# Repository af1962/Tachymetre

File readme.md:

Simple tachymètre, basé sur un Arduino mini, que j'utilise pour mesurer la vitesse de rotation de la broche de ma CNC.
L'affichage de la vitesse se fait sur un écran Oled i2c 128x32.

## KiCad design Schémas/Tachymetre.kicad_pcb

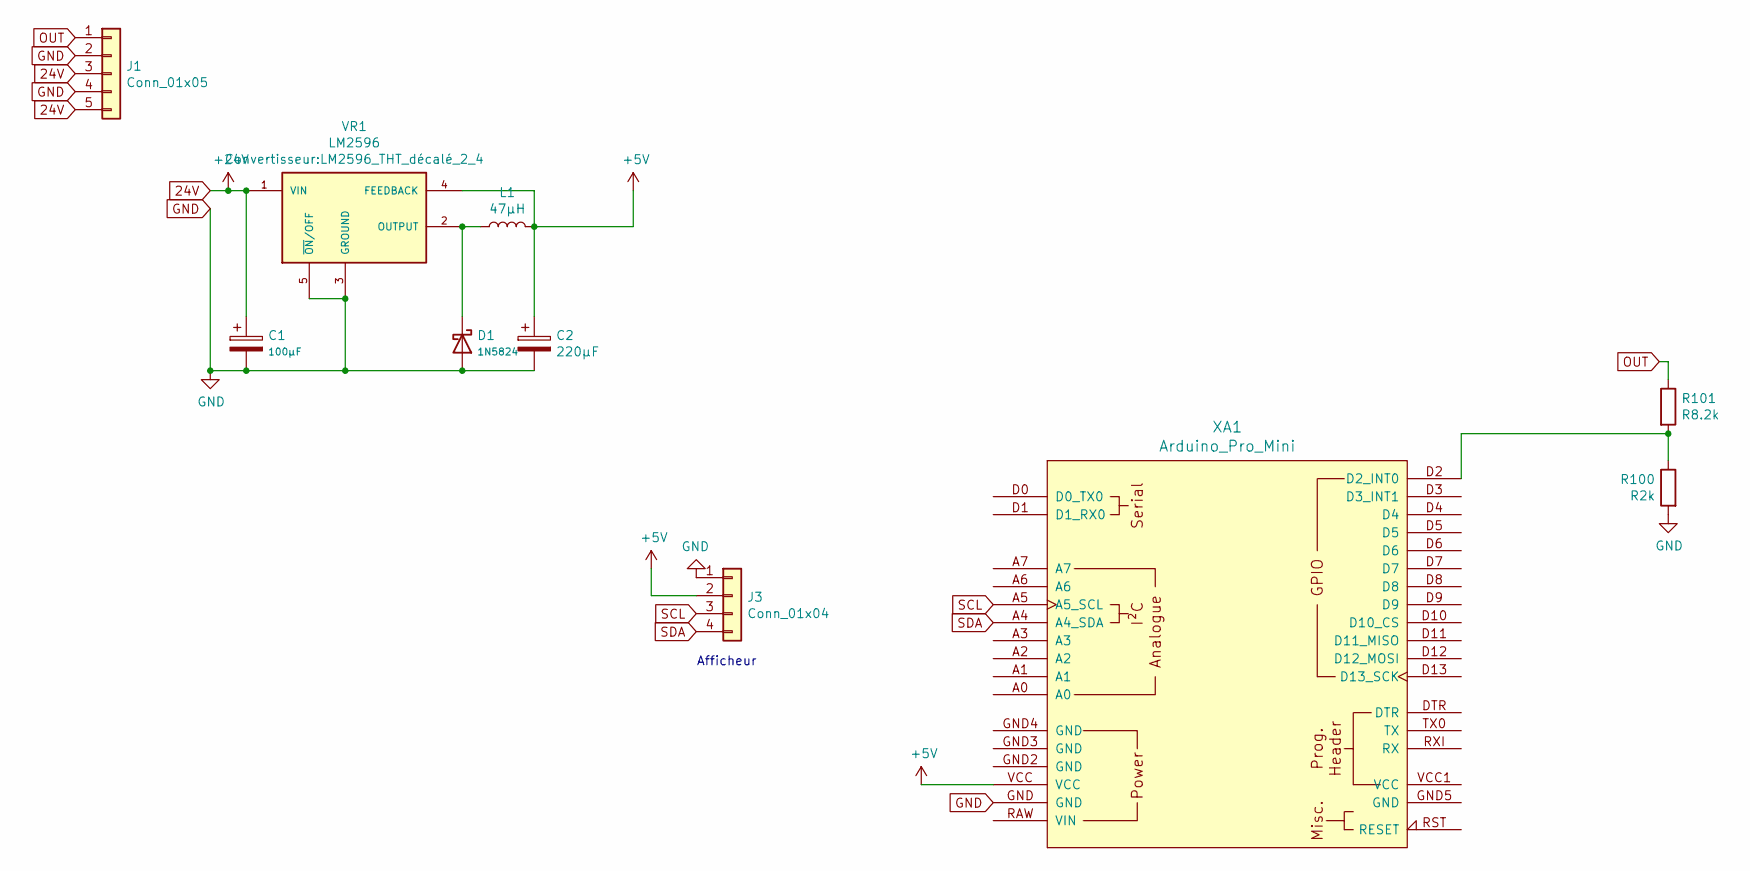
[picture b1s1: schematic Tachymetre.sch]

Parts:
C1: 100µF; CP_5x11mm
C2: 220µF; CP_10x12.5mm
D1: 1N5824; diode_do201
J1: Conn_01x05; TerminalBlock_Phoenix_MKDS-1,5-5-5.08_1x05_P5.08mm_Horizont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
J3: Conn_01x04; JST_XH_B04B-XH-A_04x2.50mm_Straight
L1: 47µH; Bobine_Toroïde
R100: R2k; R_025W
R101: R8.2k; R_025W
VR1: LM2596; LM2596_THT_décalé_2_4
XA1: Arduino_Pro_Mini

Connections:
24V: C1.1, J1.3, J1.5, VR1.1 (VIN)
+5V: C2.1, J3.2, L1.2, VR1.4 (FEEDBACK), XA1.VCC
GND: C1.2, C2.2, D1.2 (A), J1.2, J1.4, J3.1, R100.2, VR1.3 (GROUND), VR1.5 (~ON~/OFF), XA1.GND
unnamed: D1.1 (K), L1.1, VR1.2 (OUTPUT)
unnamed: R100.1, R101.2, XA1.D2 (D2_INT0)
OUT: J1.1, R101.1
SCL: J3.3, XA1.A5 (A5_SCL)
SDA: J3.4, XA1.A4 (A4_SDA)

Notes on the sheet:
Afficheur

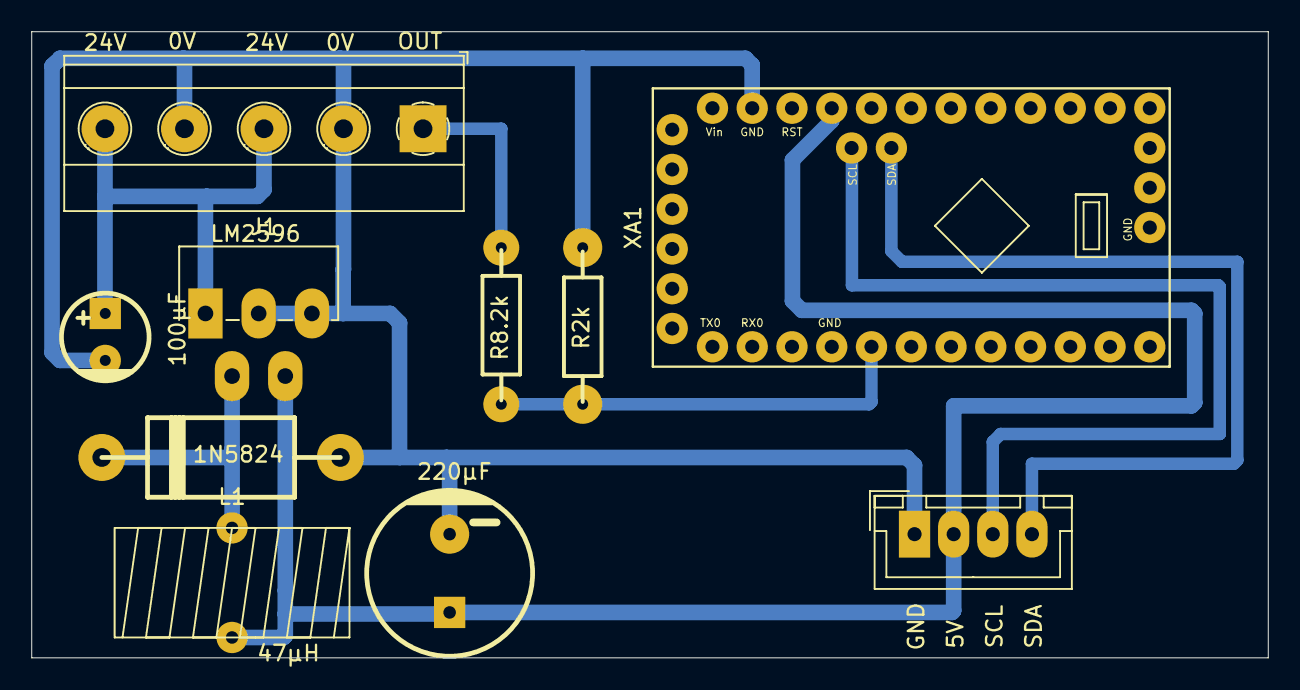
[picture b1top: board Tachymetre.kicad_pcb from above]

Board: 2 copper layers, 79.0 x 40.0 mm, 10 parts (0 on the bottom side), 8 nets.

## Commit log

2023-03-20 Init
2023-03-21 Repère Oled
2023-03-21 Mise à jour dossiers programme
2023-03-22 Commentaires
2023-05-16 Mise à jour
2023-05-16 Readme
2023-05-20 Photo
